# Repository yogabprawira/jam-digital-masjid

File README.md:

# Jam Digital Masjid

Bahan-bahan yang digunakan:
- Arduino Pro Mini 5V
- Modul RTC DS3231 (sepaket dengan EEPROM AT24C32) 
- MP1584 Buck / Step Down 3A Adjustable Regulator Module
- PCB
- Seven segment
- Resistor
- Kabel
- Power supply (adaptor dengan jack DC 12V) 

Seven segment yang digunakan:
- 4 buah seven segment untuk tampilan jam
- 6 buah seven segment untuk tampilan tanggal/hari
- 4 buah seven segment untuk tampilan jadwal x 6 (Imsyak, Shubuh, Zuhur, Asar, Maghrib, Isya)

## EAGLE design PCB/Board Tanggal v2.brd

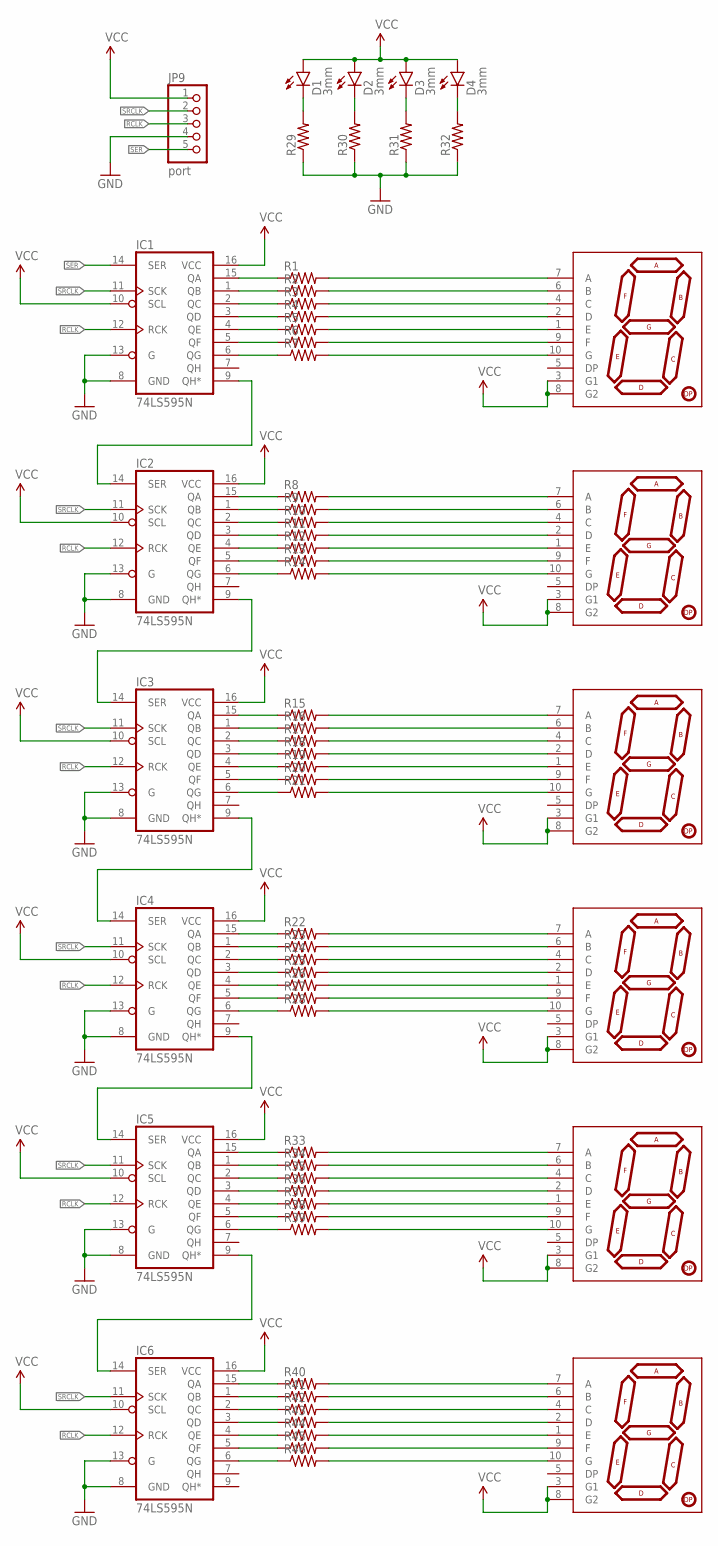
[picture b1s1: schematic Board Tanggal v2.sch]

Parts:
D1, D2, D3, D4: 3mm; LED3MM
IC1, IC2, IC3, IC4, IC5, IC6: 74LS595N; DIL16
JP9: port; 1X05
R1, R2, R3, R4, R5, R6, R7, R8, R9, R10, R11, R12, R13, R14, R15, R16, R17, R18, R19, R20, R21, R22, R23, R24, R25, R26, R27, R28, R29, R30, R31, R32, R33, R34, R35, R36, R37, R38, R39, R40, R41, R42, R43, R44, R45, R46: RESISTORPTH-1/4W; AXIAL-0.4
U$1, U$2, U$3, U$4, U$5, U$6: 7-SEGMENT-DISPLAY-1"-REDEZ; 7-SEGMENT-1"PTH-EZ

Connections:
A_0: R1.P$2 (2), U$1.7 (A)
A_2: R15.P$2 (2), U$3.7 (A)
A_3: R22.P$2 (2), U$4.7 (A)
A_4: R33.P$2 (2), U$5.7 (A)
A_5: R40.P$2 (2), U$6.7 (A)
B_0: R2.P$2 (2), U$1.6 (B)
B_1: R9.P$2 (2), U$2.6 (B)
B_2: R16.P$2 (2), U$3.6 (B)
B_3: R23.P$2 (2), U$4.6 (B)
B_4: R34.P$2 (2), U$5.6 (B)
B_5: R41.P$2 (2), U$6.6 (B)
C_0: R3.P$2 (2), U$1.4 (C)
C_1: R10.P$2 (2), U$2.4 (C)
C_2: R17.P$2 (2), U$3.4 (C)
C_3: R24.P$2 (2), U$4.4 (C)
C_4: R35.P$2 (2), U$5.4 (C)
C_5: R42.P$2 (2), U$6.4 (C)
D_0: R4.P$2 (2), U$1.2 (D)
D_1: R11.P$2 (2), U$2.2 (D)
D_2: R18.P$2 (2), U$3.2 (D)
D_3: R25.P$2 (2), U$4.2 (D)
D_4: R36.P$2 (2), U$5.2 (D)
D_5: R43.P$2 (2), U$6.2 (D)
E_0: R5.P$2 (2), U$1.1 (E)
E_1: R12.P$2 (2), U$2.1 (E)
E_2: R19.P$2 (2), U$3.1 (E)
E_3: R26.P$2 (2), U$4.1 (E)
E_4: R37.P$2 (2), U$5.1 (E)
E_5: R44.P$2 (2), U$6.1 (E)
F_0: R6.P$2 (2), U$1.9 (F)
F_1: R13.P$2 (2), U$2.9 (F)
F_2: R20.P$2 (2), U$3.9 (F)
F_3: R27.P$2 (2), U$4.9 (F)
F_4: R38.P$2 (2), U$5.9 (F)
F_5: R45.P$2 (2), U$6.9 (F)
GND: IC1.8 (GND), IC1.13 (G), IC2.8 (GND), IC2.13 (G), IC3.8 (GND), IC3.13 (G), IC4.8 (GND), IC4.13 (G), IC5.8 (GND), IC5.13 (G), IC6.8 (GND), IC6.13 (G), JP9.4, R29.P$1 (1), R30.P$1 (1), R31.P$1 (1), R32.P$1 (1)
G_0: R7.P$2 (2), U$1.10 (G)
G_1: R14.P$2 (2), U$2.10 (G)
G_2: R21.P$2 (2), U$3.10 (G)
G_3: R28.P$2 (2), U$4.10 (G)
G_4: R39.P$2 (2), U$5.10 (G)
G_5: R46.P$2 (2), U$6.10 (G)
unnamed: IC1.15 (QA), R1.P$1 (1)
unnamed: IC2.15 (QA), R8.P$1 (1)
unnamed: IC1.1 (QB), R2.P$1 (1)
unnamed: IC1.2 (QC), R3.P$1 (1)
unnamed: IC1.3 (QD), R4.P$1 (1)
unnamed: IC1.4 (QE), R5.P$1 (1)
unnamed: IC1.5 (QF), R6.P$1 (1)
unnamed: IC1.6 (QG), R7.P$1 (1)
unnamed: IC2.1 (QB), R9.P$1 (1)
unnamed: IC2.2 (QC), R10.P$1 (1)
unnamed: IC2.3 (QD), R11.P$1 (1)
unnamed: IC2.4 (QE), R12.P$1 (1)
unnamed: IC2.5 (QF), R13.P$1 (1)
unnamed: IC2.6 (QG), R14.P$1 (1)
unnamed: IC3.15 (QA), R15.P$1 (1)
unnamed: IC3.1 (QB), R16.P$1 (1)
unnamed: IC3.2 (QC), R17.P$1 (1)
unnamed: IC3.3 (QD), R18.P$1 (1)
unnamed: IC3.4 (QE), R19.P$1 (1)
unnamed: IC3.5 (QF), R20.P$1 (1)
unnamed: IC3.6 (QG), R21.P$1 (1)
unnamed: IC4.15 (QA), R22.P$1 (1)
unnamed: IC4.1 (QB), R23.P$1 (1)
unnamed: IC4.2 (QC), R24.P$1 (1)
unnamed: IC4.3 (QD), R25.P$1 (1)
unnamed: IC4.4 (QE), R26.P$1 (1)
unnamed: IC4.5 (QF), R27.P$1 (1)
unnamed: IC4.6 (QG), R28.P$1 (1)
unnamed: IC1.9 (QH*), IC2.14 (SER)
unnamed: IC2.9 (QH*), IC3.14 (SER)
unnamed: IC3.9 (QH*), IC4.14 (SER)
unnamed: D1.K (C), R29.P$2 (2)
unnamed: D2.K (C), R30.P$2 (2)
unnamed: D3.K (C), R31.P$2 (2)
unnamed: D4.K (C), R32.P$2 (2)
unnamed: IC5.15 (QA), R33.P$1 (1)
unnamed: IC5.1 (QB), R34.P$1 (1)
unnamed: IC5.2 (QC), R35.P$1 (1)
unnamed: IC5.3 (QD), R36.P$1 (1)
unnamed: IC5.4 (QE), R37.P$1 (1)
unnamed: IC5.5 (QF), R38.P$1 (1)
unnamed: IC5.6 (QG), R39.P$1 (1)
unnamed: IC4.9 (QH*), IC5.14 (SER)
unnamed: IC6.15 (QA), R40.P$1 (1)
unnamed: IC6.1 (QB), R41.P$1 (1)
unnamed: IC6.2 (QC), R42.P$1 (1)
unnamed: IC6.3 (QD), R43.P$1 (1)
unnamed: IC6.4 (QE), R44.P$1 (1)
unnamed: IC6.5 (QF), R45.P$1 (1)
unnamed: IC6.6 (QG), R46.P$1 (1)
unnamed: IC5.9 (QH*), IC6.14 (SER)
unnamed: R8.P$2 (2), U$2.7 (A)
RCLK: IC1.12 (RCK), IC2.12 (RCK), IC3.12 (RCK), IC4.12 (RCK), IC5.12 (RCK), IC6.12 (RCK), JP9.3
SER: IC1.14 (SER), JP9.5
SRCLK: IC1.11 (SCK), IC2.11 (SCK), IC3.11 (SCK), IC4.11 (SCK), IC5.11 (SCK), IC6.11 (SCK), JP9.2
VCC: D1.A, D2.A, D3.A, D4.A, IC1.10 (SCL), IC1.16 (VCC), IC2.10 (SCL), IC2.16 (VCC), IC3.10 (SCL), IC3.16 (VCC), IC4.10 (SCL), IC4.16 (VCC), IC5.10 (SCL), IC5.16 (VCC), IC6.10 (SCL), IC6.16 (VCC), JP9.1, U$1.3 (G1), U$1.8 (G2), U$2.3 (G1), U$2.8 (G2), U$3.3 (G1), U$3.8 (G2), U$4.3 (G1), U$4.8 (G2), U$5.3 (G1), U$5.8 (G2), U$6.3 (G1), U$6.8 (G2)

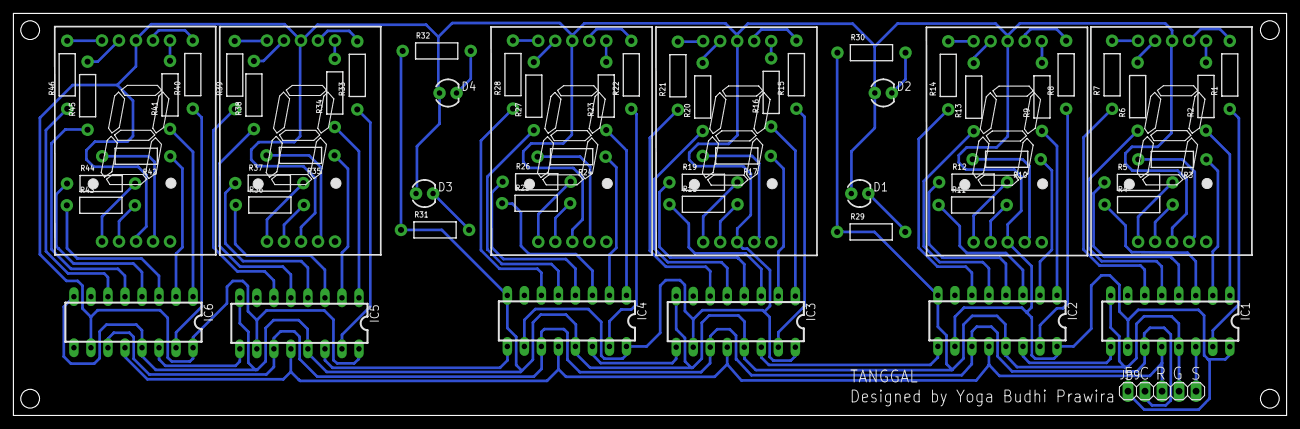
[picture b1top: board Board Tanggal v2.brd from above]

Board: 2 copper layers, 190.0 x 60.0 mm, 63 parts (0 on the bottom side), 98 nets.

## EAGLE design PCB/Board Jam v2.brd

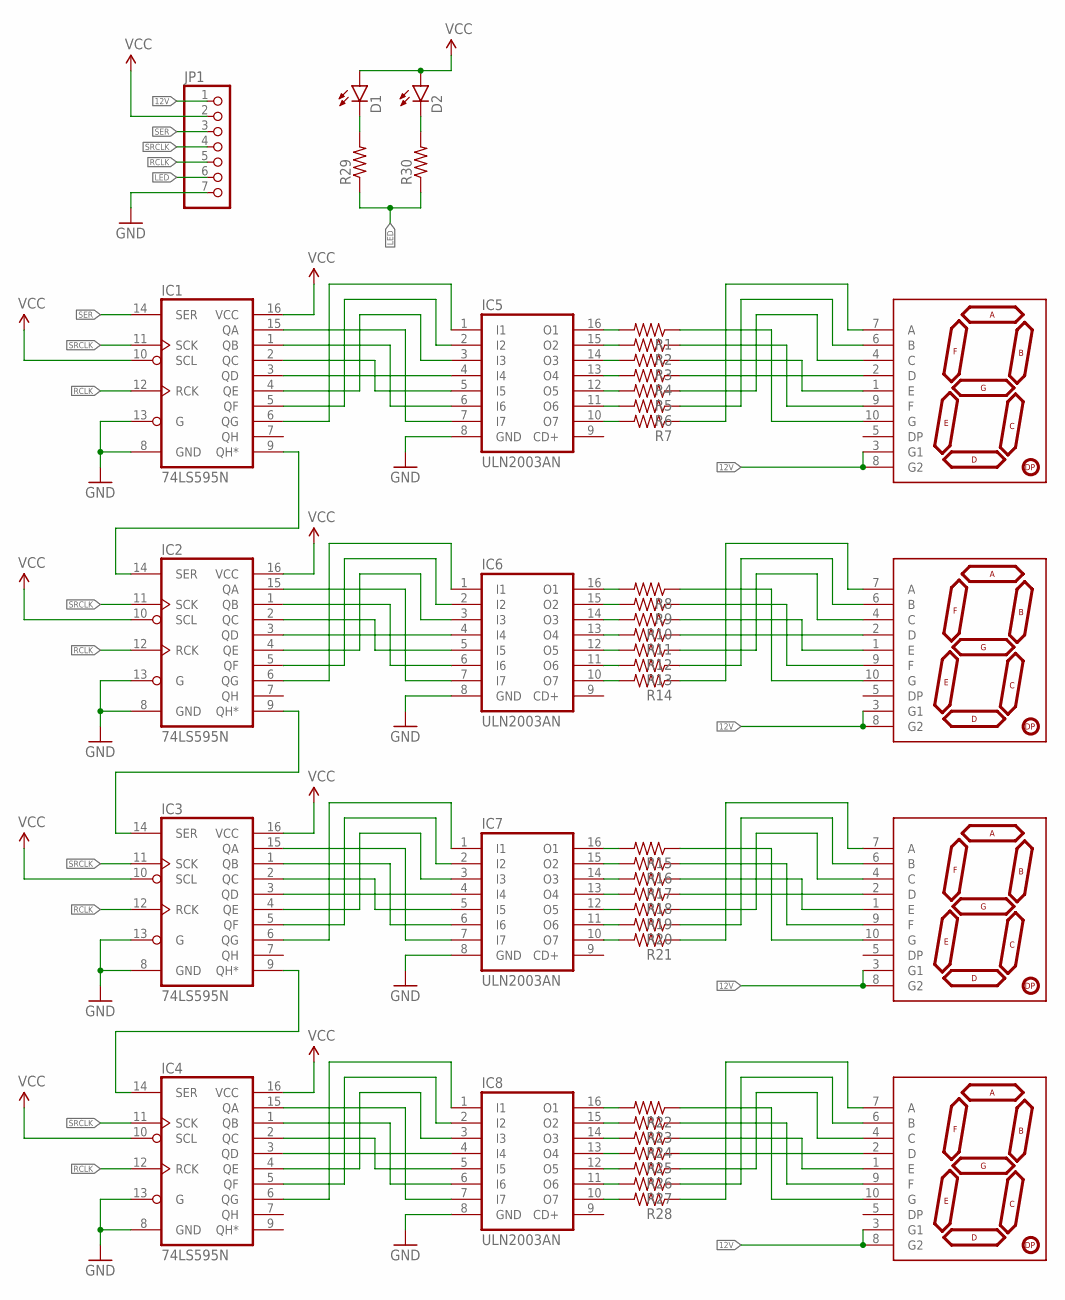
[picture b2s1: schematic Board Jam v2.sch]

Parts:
D1, D2: LED5MM
IC1, IC2, IC3, IC4: 74LS595N; DIL16
IC5, IC6, IC7, IC8: ULN2003AN; DIL16
JP1: PINHD-1X7; 1X07
R1, R2, R3, R4, R5, R6, R7, R8, R9, R10, R11, R12, R13, R14, R15, R16, R17, R18, R19, R20, R21, R22, R23, R24, R25, R26, R27, R28, R29, R30: RESISTORPTH-1/4W; AXIAL-0.4
U$1, U$2, U$3, U$4: 7-SEGMENT-DISPLAY-1"-RED7-SEGMENT-1.8"PTH; 7-SEGMENT-1"PTH

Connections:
12V: JP1.1, U$1.3 (G1), U$1.8 (G2), U$2.3 (G1), U$2.8 (G2), U$3.3 (G1), U$3.8 (G2), U$4.3 (G1), U$4.8 (G2)
GND: IC1.8 (GND), IC1.13 (G), IC2.8 (GND), IC2.13 (G), IC3.8 (GND), IC3.13 (G), IC4.8 (GND), IC4.13 (G), IC5.8 (GND), IC6.8 (GND), IC7.8 (GND), IC8.8 (GND), JP1.7
LED: JP1.6, R29.P$1 (1), R30.P$1 (1)
unnamed: IC1.15 (QA), IC5.7 (I7)
unnamed: IC2.15 (QA), IC6.7 (I7)
unnamed: IC1.1 (QB), IC5.6 (I6)
unnamed: IC1.2 (QC), IC5.5 (I5)
unnamed: IC1.3 (QD), IC5.4 (I4)
unnamed: IC1.4 (QE), IC5.3 (I3)
unnamed: IC1.5 (QF), IC5.2 (I2)
unnamed: IC1.6 (QG), IC5.1 (I1)
unnamed: IC2.1 (QB), IC6.6 (I6)
unnamed: IC2.2 (QC), IC6.5 (I5)
unnamed: IC2.3 (QD), IC6.4 (I4)
unnamed: IC2.4 (QE), IC6.3 (I3)
unnamed: IC2.5 (QF), IC6.2 (I2)
unnamed: IC2.6 (QG), IC6.1 (I1)
unnamed: IC6.16 (O1), R8.P$2 (2)
unnamed: IC6.15 (O2), R9.P$2 (2)
unnamed: IC6.14 (O3), R10.P$2 (2)
unnamed: IC6.13 (O4), R11.P$2 (2)
unnamed: IC6.12 (O5), R12.P$2 (2)
unnamed: IC6.11 (O6), R13.P$2 (2)
unnamed: IC6.10 (O7), R14.P$2 (2)
unnamed: IC3.15 (QA), IC7.7 (I7)
unnamed: IC3.1 (QB), IC7.6 (I6)
unnamed: IC3.2 (QC), IC7.5 (I5)
unnamed: IC3.3 (QD), IC7.4 (I4)
unnamed: IC3.4 (QE), IC7.3 (I3)
unnamed: IC3.5 (QF), IC7.2 (I2)
unnamed: IC3.6 (QG), IC7.1 (I1)
unnamed: IC1.9 (QH*), IC2.14 (SER)
unnamed: IC2.9 (QH*), IC3.14 (SER)
unnamed: IC3.9 (QH*), IC4.14 (SER)
unnamed: D1.K (C), R29.P$2 (2)
unnamed: D2.K (C), R30.P$2 (2)
unnamed: IC7.16 (O1), R15.P$2 (2)
unnamed: IC5.16 (O1), R1.P$2 (2)
unnamed: IC5.15 (O2), R2.P$2 (2)
unnamed: IC5.14 (O3), R3.P$2 (2)
unnamed: IC5.13 (O4), R4.P$2 (2)
unnamed: IC5.12 (O5), R5.P$2 (2)
unnamed: IC5.11 (O6), R6.P$2 (2)
unnamed: IC5.10 (O7), R7.P$2 (2)
unnamed: IC7.15 (O2), R16.P$2 (2)
unnamed: IC7.14 (O3), R17.P$2 (2)
unnamed: IC7.13 (O4), R18.P$2 (2)
unnamed: IC7.12 (O5), R19.P$2 (2)
unnamed: IC7.11 (O6), R20.P$2 (2)
unnamed: IC7.10 (O7), R21.P$2 (2)
unnamed: IC4.15 (QA), IC8.7 (I7)
unnamed: IC4.1 (QB), IC8.6 (I6)
unnamed: IC4.2 (QC), IC8.5 (I5)
unnamed: IC4.3 (QD), IC8.4 (I4)
unnamed: IC4.4 (QE), IC8.3 (I3)
unnamed: IC4.5 (QF), IC8.2 (I2)
unnamed: IC4.6 (QG), IC8.1 (I1)
unnamed: IC8.16 (O1), R22.P$2 (2)
unnamed: IC8.15 (O2), R23.P$2 (2)
unnamed: IC8.14 (O3), R24.P$2 (2)
unnamed: IC8.13 (O4), R25.P$2 (2)
unnamed: IC8.12 (O5), R26.P$2 (2)
unnamed: IC8.11 (O6), R27.P$2 (2)
unnamed: IC8.10 (O7), R28.P$2 (2)
unnamed: R1.P$1 (1), U$1.10 (G)
unnamed: R2.P$1 (1), U$1.9 (F)
unnamed: R3.P$1 (1), U$1.1 (E)
unnamed: R4.P$1 (1), U$1.2 (D)
unnamed: R5.P$1 (1), U$1.4 (C)
unnamed: R6.P$1 (1), U$1.6 (B)
unnamed: R7.P$1 (1), U$1.7 (A)
unnamed: R8.P$1 (1), U$2.10 (G)
unnamed: R9.P$1 (1), U$2.9 (F)
unnamed: R10.P$1 (1), U$2.1 (E)
unnamed: R11.P$1 (1), U$2.2 (D)
unnamed: R12.P$1 (1), U$2.4 (C)
unnamed: R13.P$1 (1), U$2.6 (B)
unnamed: R14.P$1 (1), U$2.7 (A)
unnamed: R15.P$1 (1), U$3.10 (G)
unnamed: R16.P$1 (1), U$3.9 (F)
unnamed: R17.P$1 (1), U$3.1 (E)
unnamed: R18.P$1 (1), U$3.2 (D)
unnamed: R19.P$1 (1), U$3.4 (C)
unnamed: R20.P$1 (1), U$3.6 (B)
unnamed: R21.P$1 (1), U$3.7 (A)
unnamed: R22.P$1 (1), U$4.10 (G)
unnamed: R23.P$1 (1), U$4.9 (F)
unnamed: R24.P$1 (1), U$4.1 (E)
unnamed: R25.P$1 (1), U$4.2 (D)
unnamed: R26.P$1 (1), U$4.4 (C)
unnamed: R27.P$1 (1), U$4.6 (B)
unnamed: R28.P$1 (1), U$4.7 (A)
RCLK: IC1.12 (RCK), IC2.12 (RCK), IC3.12 (RCK), IC4.12 (RCK), JP1.5
SER: IC1.14 (SER), JP1.3
SRCLK: IC1.11 (SCK), IC2.11 (SCK), IC3.11 (SCK), IC4.11 (SCK), JP1.4
VCC: D1.A, D2.A, IC1.10 (SCL), IC1.16 (VCC), IC2.10 (SCL), IC2.16 (VCC), IC3.10 (SCL), IC3.16 (VCC), IC4.10 (SCL), IC4.16 (VCC), JP1.2

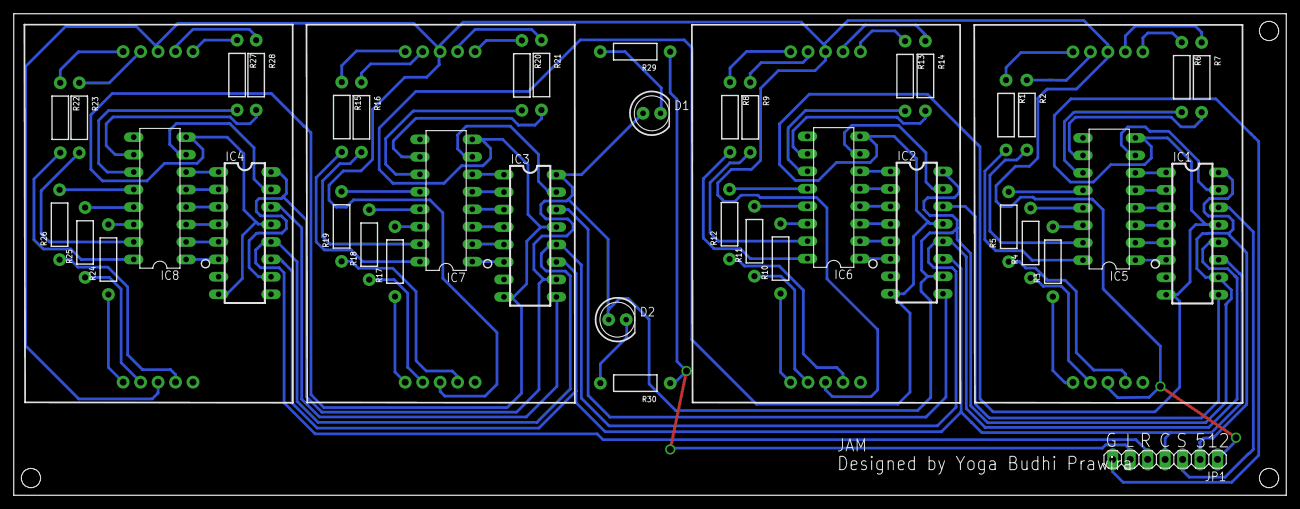
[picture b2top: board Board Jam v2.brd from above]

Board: 2 copper layers, 185.0 x 70.0 mm, 45 parts (0 on the bottom side), 96 nets.

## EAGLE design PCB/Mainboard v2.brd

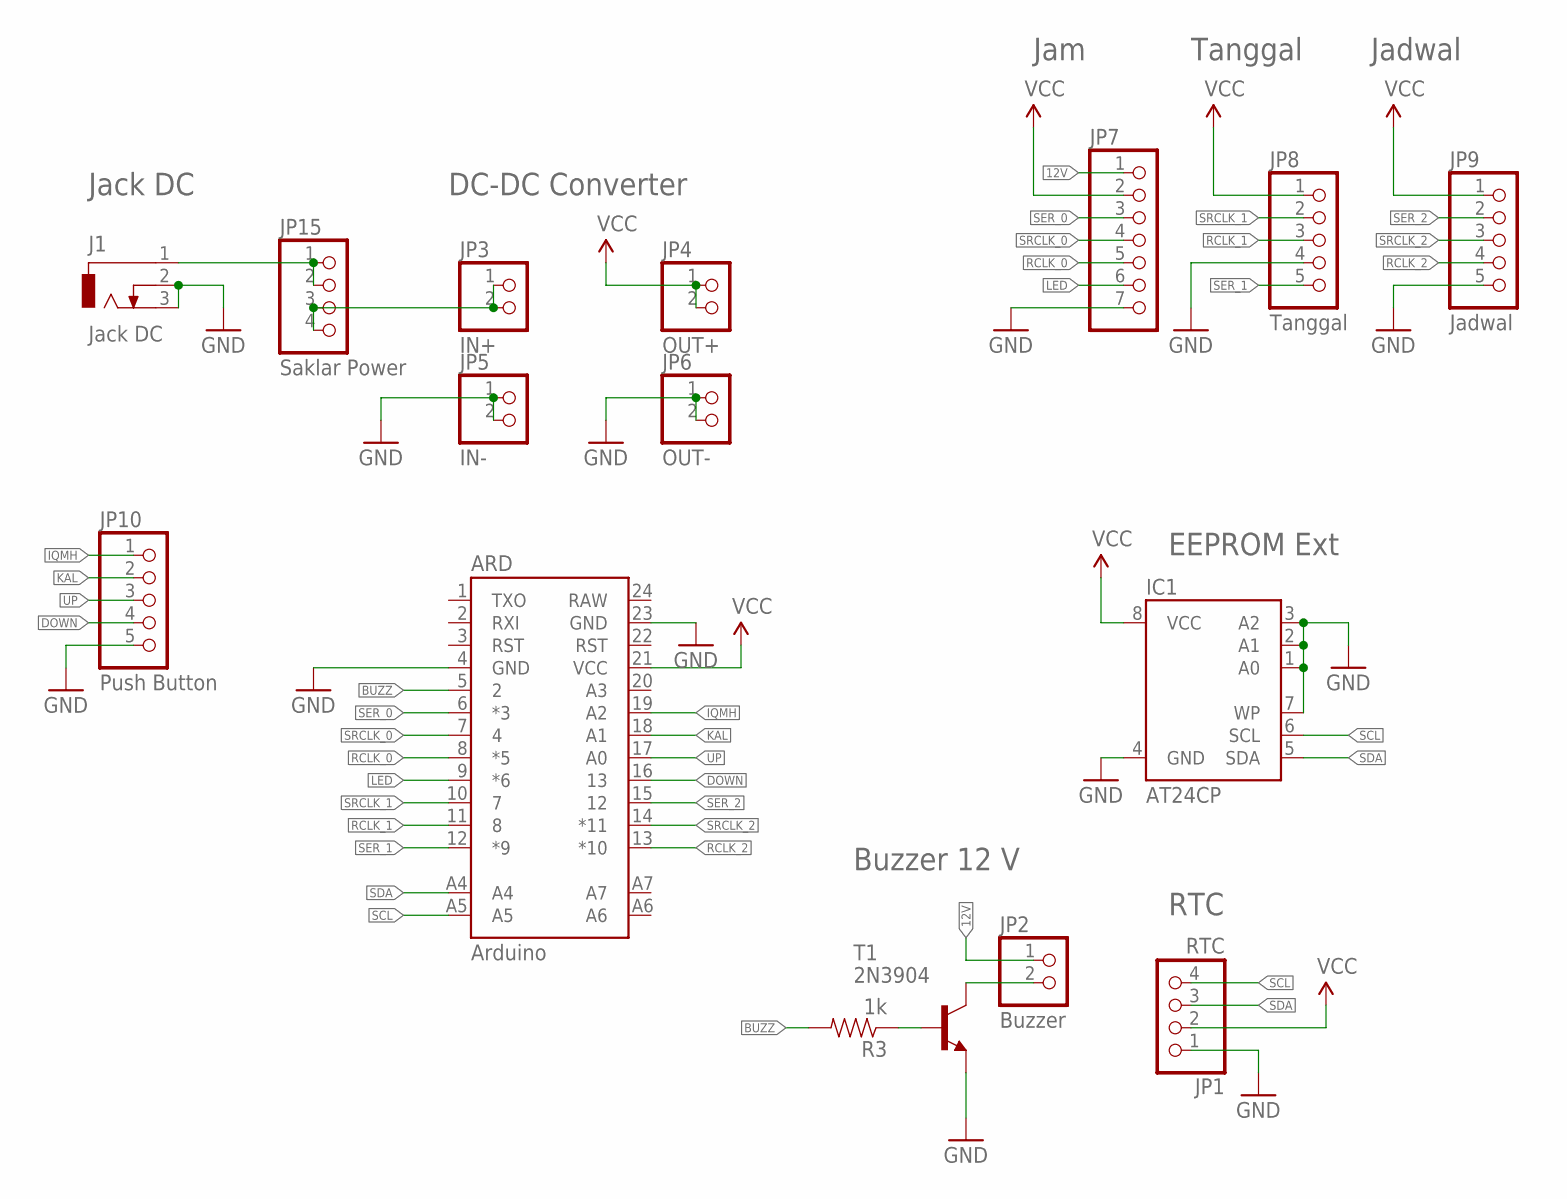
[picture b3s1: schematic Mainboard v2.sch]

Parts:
ARD: Arduino; ARDUINO_PRO_MINI
IC1: AT24CP; DIL08
J1: Jack DC; DCJ0202
JP1: RTC; 1X04
JP2: Buzzer; 1X02
JP3: IN+; 1X02
JP4: OUT+; 1X02
JP5: IN-; 1X02
JP6: OUT-; 1X02
JP7: PINHD-1X7; 1X07
JP8: Tanggal; 1X05
JP9: Jadwal; 1X05
JP10: Push Button; 1X05
JP15: Saklar Power; 1X04
R3: 1k; AXIAL-0.4
T1: 2N3904; TO92

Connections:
12V: JP2.1, JP3.1, JP3.2, JP7.1, JP15.3, JP15.4
BUZZ: ARD.5 (2), R3.P$2 (2)
DOWN: ARD.16 (13), JP10.4
GND: ARD.4 (GND), ARD.23 (GND), IC1.1 (A0), IC1.2 (A1), IC1.3 (A2), IC1.4 (GND), IC1.7 (WP), J1.2, J1.3, JP1.1, JP5.1, JP5.2, JP6.1, JP6.2, JP7.7, JP8.4, JP9.5, JP10.5, T1.3 (E)
IQMH: ARD.19 (A2), JP10.1
KAL: ARD.18 (A1), JP10.2
LED: ARD.9 (*6), JP7.6
unnamed: R3.P$1 (1), T1.2 (B)
unnamed: J1.1, JP15.1, JP15.2
unnamed: JP2.2, T1.1 (C)
RCLK_0: ARD.8 (*5), JP7.5
RCLK_1: ARD.11 (8), JP8.3
RCLK_2: ARD.13 (*10), JP9.4
SCL: ARD.A5, IC1.6 (SCL), JP1.4
SDA: ARD.A4, IC1.5 (SDA), JP1.3
SER_0: ARD.6 (*3), JP7.3
SER_1: ARD.12 (*9), JP8.5
SER_2: ARD.15 (12), JP9.2
SRCLK_0: ARD.7 (4), JP7.4
SRCLK_1: ARD.10 (7), JP8.2
SRCLK_2: ARD.14 (*11), JP9.3
UP: ARD.17 (A0), JP10.3
VCC: ARD.21 (VCC), IC1.8 (VCC), JP1.2, JP4.1, JP4.2, JP7.2, JP8.1, JP9.1

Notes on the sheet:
RTC
EEPROM Ext
Buzzer 12 V
DC-DC Converter
Jam
Tanggal
Jadwal
Jack DC

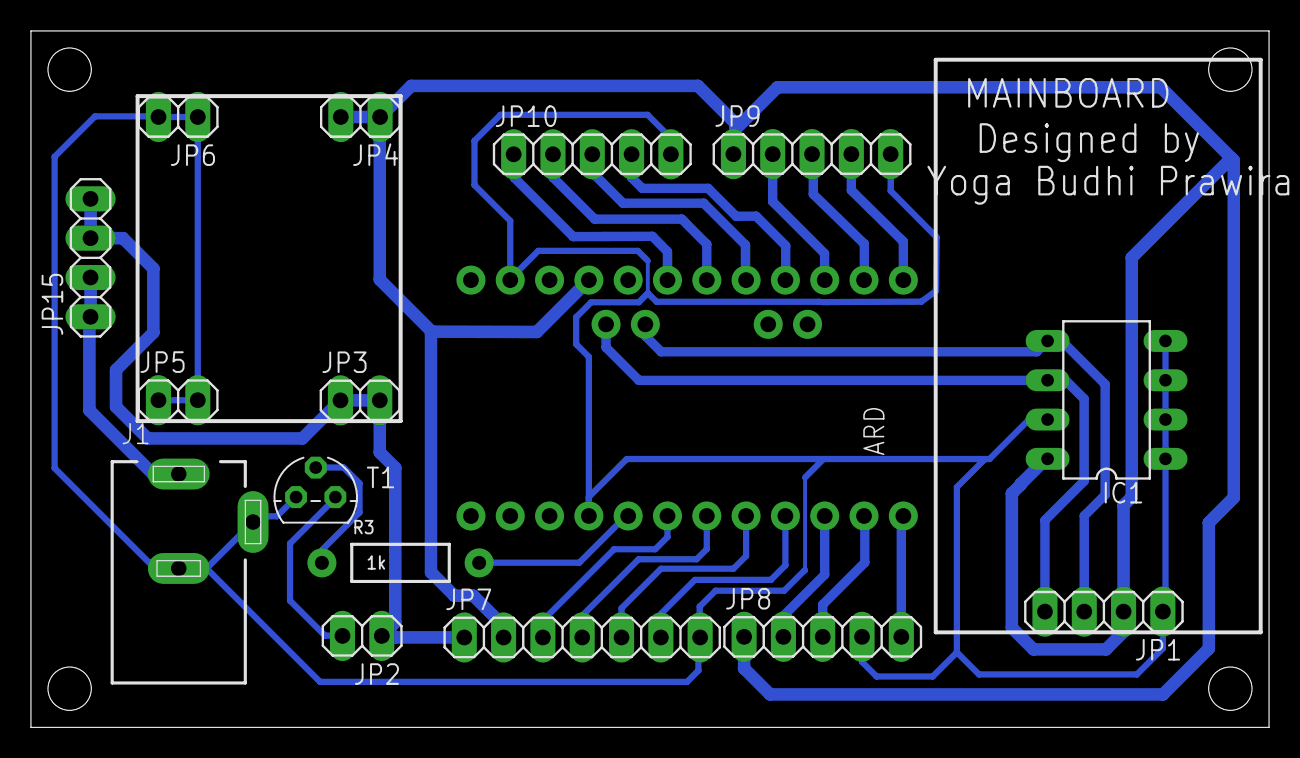
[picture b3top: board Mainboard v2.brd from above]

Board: 2 copper layers, 80.0 x 45.0 mm, 16 parts (0 on the bottom side), 23 nets.

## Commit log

2017-03-04 initial files commit
2017-03-04 Edit readme
2017-03-04 add gitignore
2017-03-04 Menghapus buzzer dan led jam library
2017-03-04 Menambah folder .build di .gitignore
2017-03-04 memindahkan PCB ke repository sendiri

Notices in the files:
parts and their libraries:
SparkFun-DigitalIC: Licensing: Creative Commons ShareAlike 4.0 International - https://creativecommons.org/licenses/by-sa/4.0
